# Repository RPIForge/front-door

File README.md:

# RPI Forge Door 

This application is the code base for the [The RPI Forge's](https://theforge.rpi.edu/) door. The code is written in Python 3.6.8 and integrates with google calendar, slack, and physical switches.

The application requires a folder `include\credentials\` that has a `token.pkl` that contains your google calendar credentials that can be obtained [here](https://developers.google.com/calendar/quickstart/python)

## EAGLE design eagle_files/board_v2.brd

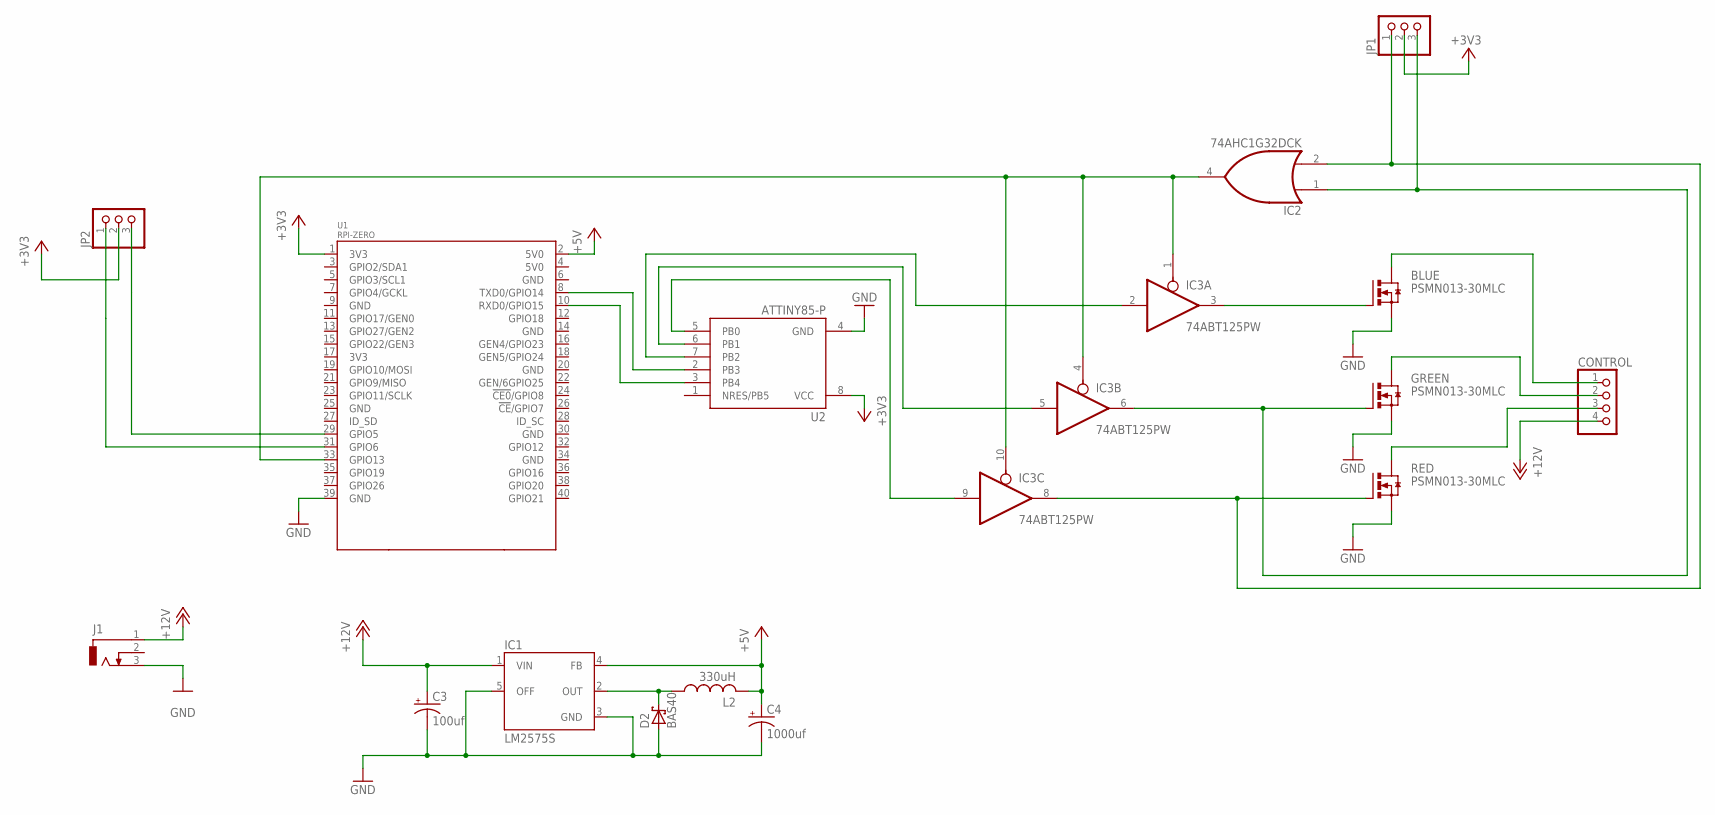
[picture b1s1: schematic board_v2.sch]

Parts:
BLUE: PSMN013-30MLC; LFPAK33
C3: 100uf; A/3216-18R
C4: 1000uf; A/3216-18R
CONTROL: PINHD-1X4; 1X04
D2: BAS40; SOT23
GREEN: PSMN013-30MLC; LFPAK33
IC1: LM2575S; TO263-5
IC2: 74AHC1G32DCK; SC70-5
IC3: 74ABT125PW; TSSOP14
J1: DCJ0303
JP1, JP2: PINHD-1X3; 1X03
L2: 330uH; L1812
RED: PSMN013-30MLC; LFPAK33
U1: RPI-ZERO; RASPBERRYPI_BASTELSTUBE_V13_RASPI_BOARD_B+_FULL
U2: ATTINY85-P; PDIP08_300MIL

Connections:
+3V3: JP1.2, JP2.2, U1.1 (3V3), U2.8 (VCC)
+5V: C4.+, IC1.4 (FB), L2.2, U1.2 (5V0)
+12V: C3.+, CONTROL.4, IC1.1 (VIN), J1.1
BLUE: IC3.2 (I), U2.7 (PB2)
GND: BLUE.1 (S), BLUE.2 (S), BLUE.3 (S), C3.-, C4.-, D2.1 (A), GREEN.1 (S), GREEN.2 (S), GREEN.3 (S), IC1.3 (GND), IC1.5 (OFF), IC2.3 (GND), IC3.7 (GND), J1.3, RED.1 (S), RED.2 (S), RED.3 (S), U1.39 (GND), U2.4 (GND)
GREEN: IC3.5 (I), U2.6 (PB1)
unnamed: BLUE.MB (D), CONTROL.1
unnamed: D2.3 (C), IC1.2 (OUT), L2.1
unnamed: CONTROL.2, GREEN.MB (D)
unnamed: CONTROL.3, RED.MB (D)
unnamed: IC2.2 (I1), IC3.8 (O), JP1.1, RED.4 (G)
unnamed: GREEN.4 (G), IC2.1 (I0), IC3.6 (O), JP1.3
unnamed: BLUE.4 (G), IC3.3 (O)
unnamed: IC2.4 (O), IC3.1 (OE), IC3.4 (OE), IC3.10 (OE), U1.33 (GPIO13)
unnamed: JP2.3, U1.29 (GPIO5)
unnamed: JP2.1, U1.31 (GPIO6)
RED: IC3.9 (I), U2.5 (PB0)
RX: U1.10 (RXD0/GPIO15), U2.3 (PB4)
TX: U1.8 (TXD0/GPIO14), U2.2 (PB3)
VCC: IC2.5 (VCC), IC3.14 (VCC)

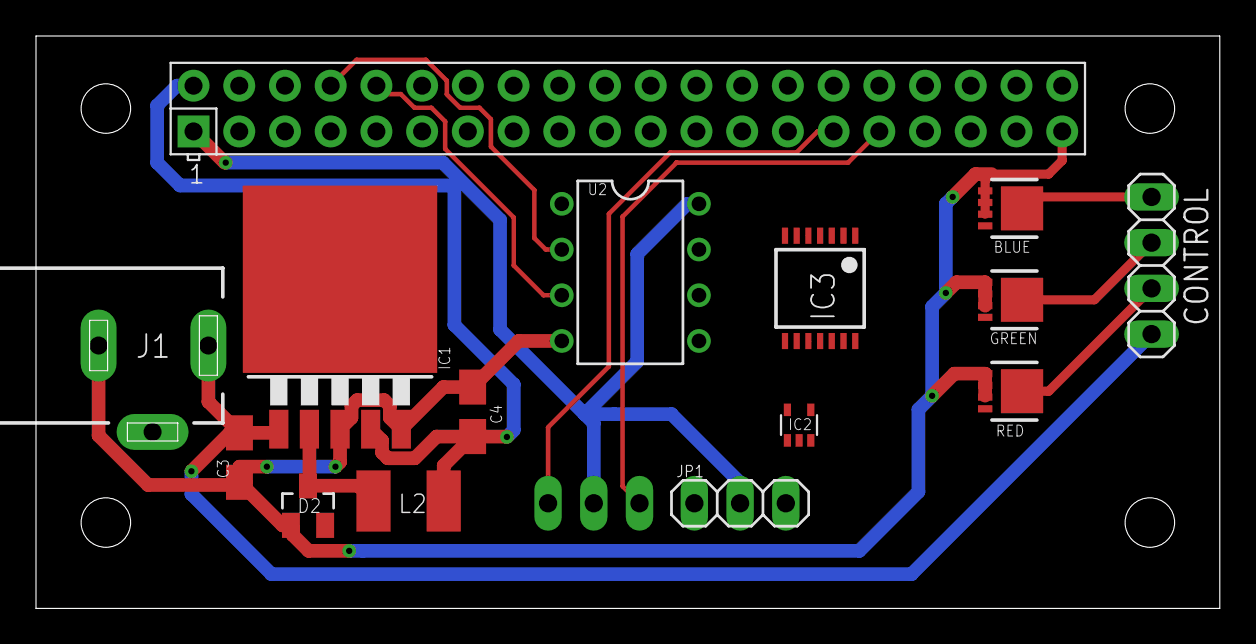
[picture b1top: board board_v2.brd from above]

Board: 2 copper layers, 65.8 x 31.8 mm, 16 parts (1 on the bottom side), 20 nets.

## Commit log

2019-11-28 First commit that keeps it upto date with previous versions
2019-11-28 Updated README with changes
2019-12-01 simplifying google calendar calls
2019-12-01 Refactored calendar code to be faster and more reliable
    I changed the calendar code to align more with the forge website as well
2020-02-13 Start of refactor
2020-02-23 Added alot of code to the slack and calendar functions. Reograni
2020-02-23 Added multiple commands and am almost ready to deploy update
2020-02-23 Updated refactor
2020-02-25 Added get current Events to calendar
2020-07-21 Added eagle files to refactor
2020-07-25 Updated logger to delete old files.
    This should fix the issue of usign up to much space. It only checks on startup but that is a latter issue
2020-07-25 Remove test file
2020-07-25 Fixed google calendar check
2020-09-10 Updated utilities and main
2020-09-11 Updated ip address
2020-09-11 Updated calendar and reset functionality
2020-09-21 Updated logging
2020-09-21 Updated startup sequence
2020-09-21 Updated led strip imports
2020-09-21 Removed print statement
2020-09-21 Removed channel restrctions and append logs
2020-09-21 Updated file mode
2020-09-21 Updated TEST
2020-09-22 Updated error handling
2020-09-22 Updated error message
2020-09-22 Updated slack error message

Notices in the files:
parts and their libraries:
transistor-power: PSMN013-30MLC © NXP B.V. 2012. All rights reserved.
